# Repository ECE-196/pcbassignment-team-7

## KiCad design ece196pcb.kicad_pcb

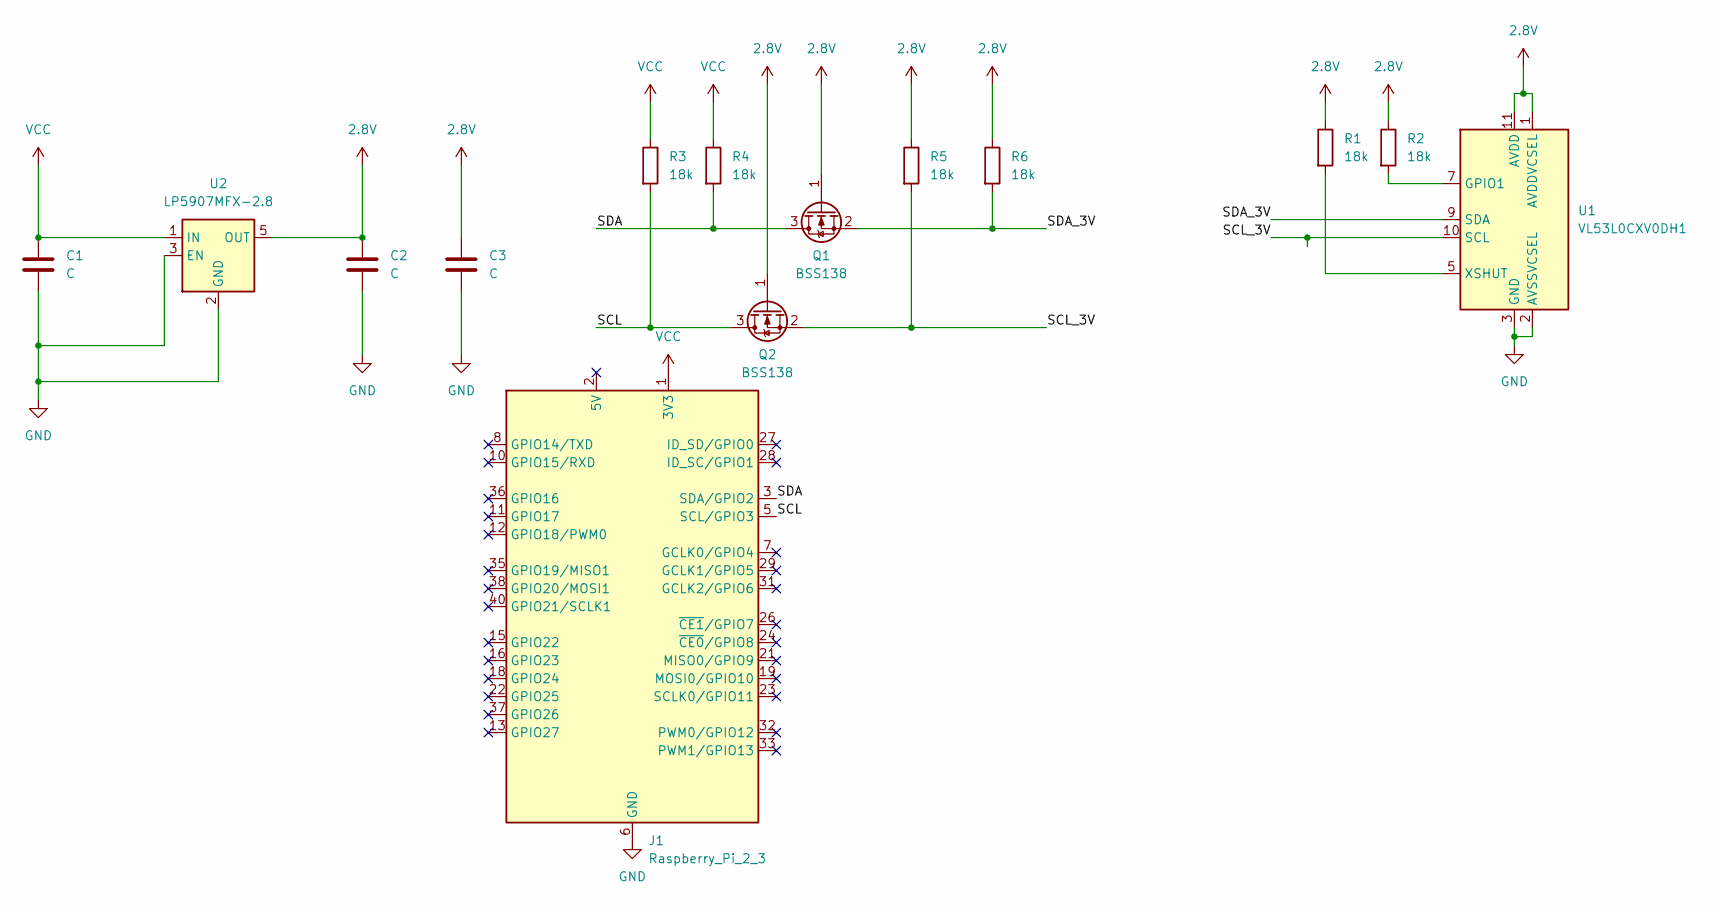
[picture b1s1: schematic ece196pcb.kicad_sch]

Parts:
C1, C2, C3: C; C_0805_2012Metric
J1: Raspberry_Pi_2_3; PinHeader_2x20_P2.54mm_Vertical
Q1, Q2: BSS138; SOT-23
R1, R2, R3, R4, R5, R6: 18k; R_0805_2012Metric_Pad1.20x1.40mm_HandSolder
U1: VL53L0CXV0DH1; ST_VL53L1x
U2: LP5907MFX-2.8; SOT-23-5

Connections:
2.8V: C2.1, C3.1, Q1.1 (G), Q2.1 (G), R1.1, R2.1, R5.1, R6.1, U1.1 (AVDDVCSEL), U1.11 (AVDD), U2.5 (OUT)
/SCL: J1.5 (SCL/GPIO3), Q2.3 (D), R3.2
/SCL_3V: Q2.2 (S), R5.2, U1.10 (SCL)
/SDA: J1.3 (SDA/GPIO2), Q1.3 (D), R4.2
/SDA_3V: Q1.2 (S), R6.2, U1.9 (SDA)
GND: C1.2, C2.2, C3.2, J1.6 (GND), J1.9 (GND), J1.14 (GND), J1.20 (GND), J1.25 (GND), J1.30 (GND), J1.34 (GND), J1.39 (GND), U1.2 (AVSSVCSEL), U1.3 (GND), U1.4 (GND), U1.6 (GND), U1.12 (GND), U2.2 (GND), U2.3 (EN)
unnamed: J1.2 (5V), J1.4 (5V)
unnamed: R2.2, U1.7 (GPIO1)
unnamed: R1.2, U1.5 (XSHUT)
VCC: C1.1, J1.1 (3V3), J1.17 (3V3), R3.1, R4.1, U2.1 (IN)

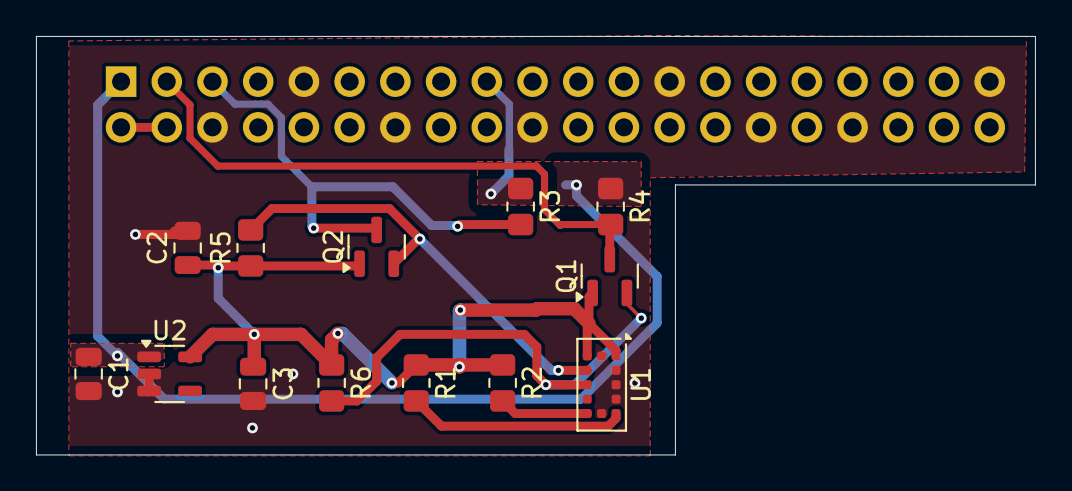
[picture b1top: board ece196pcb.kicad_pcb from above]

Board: 2 copper layers, 55.5 x 23.2 mm, 14 parts (1 on the bottom side), 10 nets.

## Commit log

2024-04-26 add deadline
2024-04-28 adding the schematic
2024-05-01 adding new schematic and layout
2024-05-03 adding gerber files to submission
2024-05-06 readding exports
2024-05-06 adding pcb
